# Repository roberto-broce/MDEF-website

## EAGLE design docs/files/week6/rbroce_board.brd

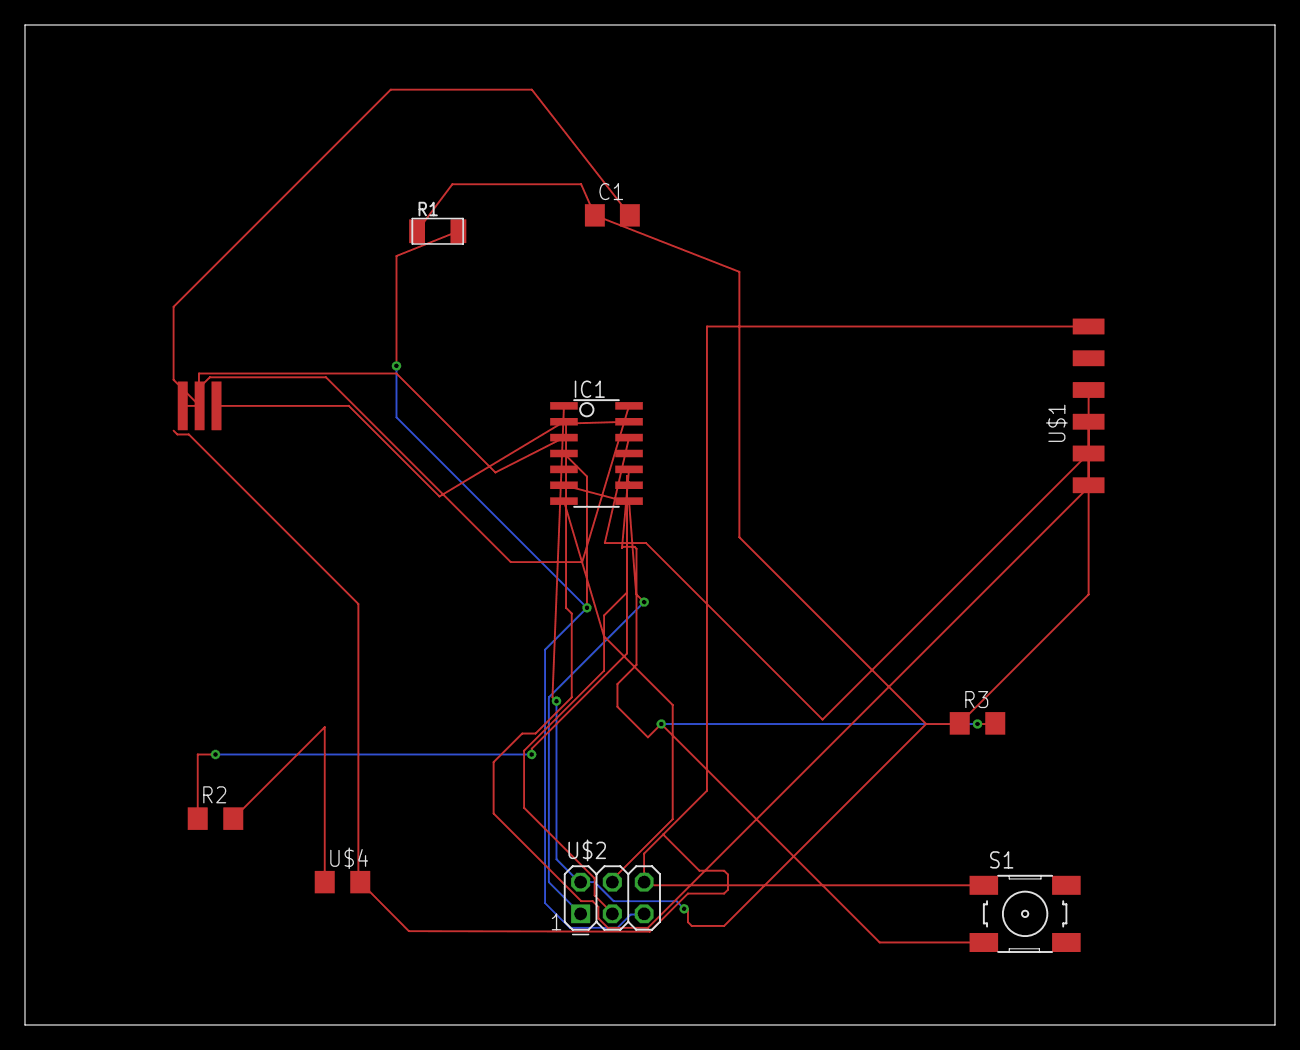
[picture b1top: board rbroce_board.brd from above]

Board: 2 copper layers, 100.0 x 80.0 mm, 10 parts (0 on the bottom side), 13 nets.

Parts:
C1: C1206
IC1: ATTINY44-SSU; SOIC14
R1: R1206FAB
R2, R3: R1206
S1: 6MM_SWITCH
U$1: FTDI-SMD-HEADER; 1X06SMD
U$2: AVRISP; 2X03
U$3: RESONATOR; EFOBM
U$4: LED; LED1206

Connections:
BUTTON: IC1.10, R3.2, S1.3
GND: C1.2, IC1.14, S1.1, U$1.1, U$2.6, U$3.2, U$4.2
LED: IC1.6, R2.1
MISO: IC1.8, U$2.1
MOSI: IC1.7, U$2.4
unnamed: R2.2, U$4.1
PB0: IC1.2, U$3.3
PB1: IC1.3, U$3.1
RST: IC1.4, R1.2, U$2.5
RX: IC1.12, U$1.5
SCK: IC1.9, U$2.3
TX: IC1.13, U$1.4
VCC: C1.1, IC1.1, R1.1, R3.1, U$1.3, U$2.2

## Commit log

2021-10-07 deploy: 3f485593245c9622cf53b14ca743f2ce14824423
2021-10-07 My First Commit
2021-10-07 deploy: 0617ae6fdb98f5cd046f69b5b1ca77ef0e1a1033
2021-10-07 edit index
2021-10-09 bootstrap template added
2021-10-09 deploy: 17eb8b85df6792abfb48e971a45656463a9a0e64
2021-10-09 Edited homepage
2021-10-09 deploy: 272036cfb63d8b98ed950da974ccc00eb0d8b5a1
2021-10-09 attempt 1 to fix website
2021-10-10 deleted mkdocs
2021-10-10 added mkdocs
2021-10-10 deploy: 75e1ead036ff964b04e3efdad882b404f083dd5d
2021-10-10 attempt to fix website 2.0
2021-10-10 deploy: 945ae316347846dec4bfa6585730f9e9d7346888
2021-10-10 deleted gitkeep
2021-10-10 restored gitkeep and added bootstrap files to docs
2021-10-10 deploy: 38be5beabbddfeb615810c89a9e6a3a090ae2f86
2021-10-10 edited about me section and menu
2021-10-10 deploy: 57a31b420644829c1d427082f66d4812d430fcfa
2021-10-10 changed weekly images in homepage and created bootcamp page
2021-10-10 deploy: 4719661b0ff4e8fff99253757a73cdc5dfe062cc
2021-10-10 bootcamp page almost complete
2021-10-10 deploy: 52f949caea367d3a40a379637f5d2441aa5b42c3
2021-10-11 fixing desired professional identity
2021-10-11 deploy: 75bde78a4b09d6eaef334aa1ae37bbdd57653e17
2021-10-11 Draft Personal Development Plan
2021-10-11 deploy: baa72f6c2b6a76f23b791c06f724f1ba6dd987cd
2021-10-11 menu fixed
2021-10-11 deploy: 79039ae72436845ba6867015d24dffd56dc684c5
2021-10-20 fixed personal development plan
2021-10-20 deploy: de61930ebec3ed595c3f25faef486f107205bd70
2021-10-20 Added AoWS
2021-10-20 deploy: f79ec2ffab4920fc02a785c5160c6c2d5c34db62
2021-10-21 finished aows page
2021-10-21 deploy: f38ba8bf5c63605fd5db9f76f540641319ea93a0
2021-10-21 added downloadable files
2021-10-21 deploy: 2b3b849f0a3ff358c32cf6d5b0ac0e43640ae01d
2021-10-31 updated design studio page
2021-10-31 deploy: 968da34edfe269d9a55e9d5c18f8a5f23a85e56b
2021-11-15 bio and agri zero
2021-11-15 deploy: b56f96d47ca7f8b9dacccf0d3213caca4cdaa47e
2021-11-22 Tech Beyond the Myth Documentation
2021-11-22 deploy: 729f940f5242dbd52152b9fcc62efa673471a014
2021-11-24 design studio adjustment
2021-11-24 deploy: 9a8324df6db658ff58deaf04589be48b7499012d
2021-11-24 bio zero page updated
2021-11-24 deploy: 9259dba42642bc40adcbb2195fcae87d57195576
2021-11-26 TBTM video n presentation
2021-11-26 deploy: 5c5cb0619fa667b40f1a307dca939b09331297cb
2021-11-26 edited About Me
2021-11-26 deploy: aef95308df36c138f6812d7b3b5c4f1b2a94a52f
2021-11-29 community
2021-11-29 deploy: d50c362f865666c0177efa5e66a43eaa53ceb3e4
2021-12-14 own ideas
2021-12-14 deploy: 9019d94ef06d8a3fd2f6c36b116cc337c695a873
2021-12-17 Half of extended inteligences
2021-12-17 deploy: dc61dc2a94fb5e95c26d6dc5ac4ed751e6ddb0a5
2021-12-19 extended intelligences complete
2021-12-19 deploy: 2d7ae7e26af268a58736ad40ecb53d7d8d8a15c5
2022-01-05 intervention
2022-01-05 deploy: 1c56aee9df5fa6aa6211ab37afae949aeccba7db
2022-01-10 Livin own ideas update
2022-01-10 deploy: 45dc74cad8a3ab0920499294b0de36fc11f74c09
2022-01-11 Tech update
2022-01-11 deploy: b4bcdc6eddb75235b4e1c4258d13e3a0ffbe25a1
2022-01-26 adjusted menu bar
2022-01-26 deploy: e3ecfd4a9db2351ae250157099eab6903e49577c
2022-02-02 profile pic
2022-02-02 deploy: 03a5f7afa18a3cf0b45d1153d6e6eda25ba910bc
2022-02-02 fight poster 2
2022-02-02 deploy: 33b41d49e49077cb650dd45e5216f32e03b3171d
2022-02-04 Design Studio 2 update w new design space
2022-02-04 deploy: 2eb56c729a9058f5b22b64ab9edf68da3553856f
2022-02-08 second design intervention
2022-02-08 deploy: 347227bc821ee8296c32128f5888ea9de6a9b7bc
2022-02-09 second week fab academy
2022-02-09 deploy: ebbd6b31eae66ab21c516b9129fbd11f9db0d07b
2022-02-09 second week fixed 2d
2022-02-09 deploy: f19e26608368b07461ade76eb092aea8cbb0e9d5
2022-02-10 week 1 fab academy and term 2 banners
2022-02-10 deploy: 446ff603fabea3b841b7193c18fed330715b8818
2022-02-10 fab academy page
2022-02-10 deploy: 796ed9a35854dc1b8a4fbdaa64244bc66e1af2b7
2022-02-10 fixed banners index
2022-02-10 deploy: c23234a5cdd43ec68b38f3e8f3b8a085a3f49221
2022-02-16 documentation week 3 fab academy
2022-02-16 deploy: bbad62331816c5c6b11c1655a76c8fea072b6132
2022-02-18 micro challenge 1
2022-02-18 deploy: 1dde966e0b19a2ae3efbfcb51d94afd18557132e
2022-02-21 fixed links w1
2022-02-21 deploy: ac8a31ee67c526f1f531d6d7ca2d6ed67ae72688
2022-02-25 biomaterials
2022-02-25 deploy: b2e6fe53ea556867b8df755cf699c2d49a766787
2022-03-01 week 4 fab academy
2022-03-01 deploy: e8acf8029e3be7af1227a2d27c8aca4ec6f7fa74
2022-03-01 week 5 fab academy
2022-03-01 deploy: 93535f7dc6f706542d8a607ed8bbda98cfa94956
2022-03-01 added downloadables
2022-03-01 deploy: 9f8e78b7b598f88dcdf96b20b8d27919afd33adf
2022-03-09 micro challenge fix
2022-03-09 deploy: 0086dfb99a461417b719ad254365393df149ba20
2022-03-15 week 6 fab academy
2022-03-15 deploy: ebb39fef90fd902092788326af1eeff722762943
2022-03-17 abstract ms&m
2022-03-18 Making sense abstact
2022-03-18 deploy: 2dcaeba254f261fec0dd056a8e58f4f852b6731b
2022-03-20 aows2
2022-03-20 deploy: cbe0ed012a1c6e7dc44140229fbcaf29b93aa2d7
2022-03-21 edits
2022-03-21 deploy: 9edc93123d8a0eeec88dec9ed53536aac1b92e3e
2022-04-27 making sense essay
2022-04-27 deploy: 75d14e560554334f9a1b07397fac5a5d2ca5cd7b
2022-05-10 micro challenge 2
2022-05-10 deploy: 958e42c0a8fde00debe11b20175f321d2378067f
2022-05-30 design ethics
2022-05-30 deploy: cbff8684c98eb4042198904261d2ed25ce491f7b
2022-05-30 week 16 F.A.
2022-05-30 deploy: 6ca2891ccf2f20ef410fdd02e0c0379cb68b570b
2022-05-30 reduced gif size
2022-05-30 deploy: b508773c7ff7430c0a31ccb0d44208def296be0b
2022-06-01 week 17
2022-06-01 deploy: 0f22525391f3635e3bebde927615836cf1296a0a
2022-06-03 week 18 fab academy
2022-06-03 deploy: d61b521ef9ce3a29b4ab02a0d9ea40a6c80c3878
2022-06-07 output and input weeks
2022-06-07 deploy: 1008408ca0cb852e9bf9d8b67b2ef241e4d0d1d7
2022-06-07 micro challenge 4
2022-06-07 deploy: ffe400b2bd2e9e66f3c7fa24af4c66b359e8158e
2022-06-08 molding
2022-06-08 deploy: 5b23fdd5703e543e9289d9e3b5002cdbc047a0ef
2022-06-13 week 14 and 15
2022-06-13 deploy: d8f2359636818736e1b323b25ed28cadb90da3f8
2022-10-11 final project link
2022-10-11 deploy: 13223718ea0f565d5d21be0e103d40a903cd691f
